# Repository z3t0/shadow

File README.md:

# SumoDuino 

### What is this repository for?
**Project Name: SumoDuino**

**Project Summary: AVR based project using to create a SumoBot**

**Version: 1.1**

### Features
* Seek and find navigation system
* Line-Sensing logic to keep robot in the ring
* Several InfraRed sensors to allow accurate seeking

### Credits
Rafi Khan, I am the owner and main contributor to this repository.
Email: zetoslab@gmail.com

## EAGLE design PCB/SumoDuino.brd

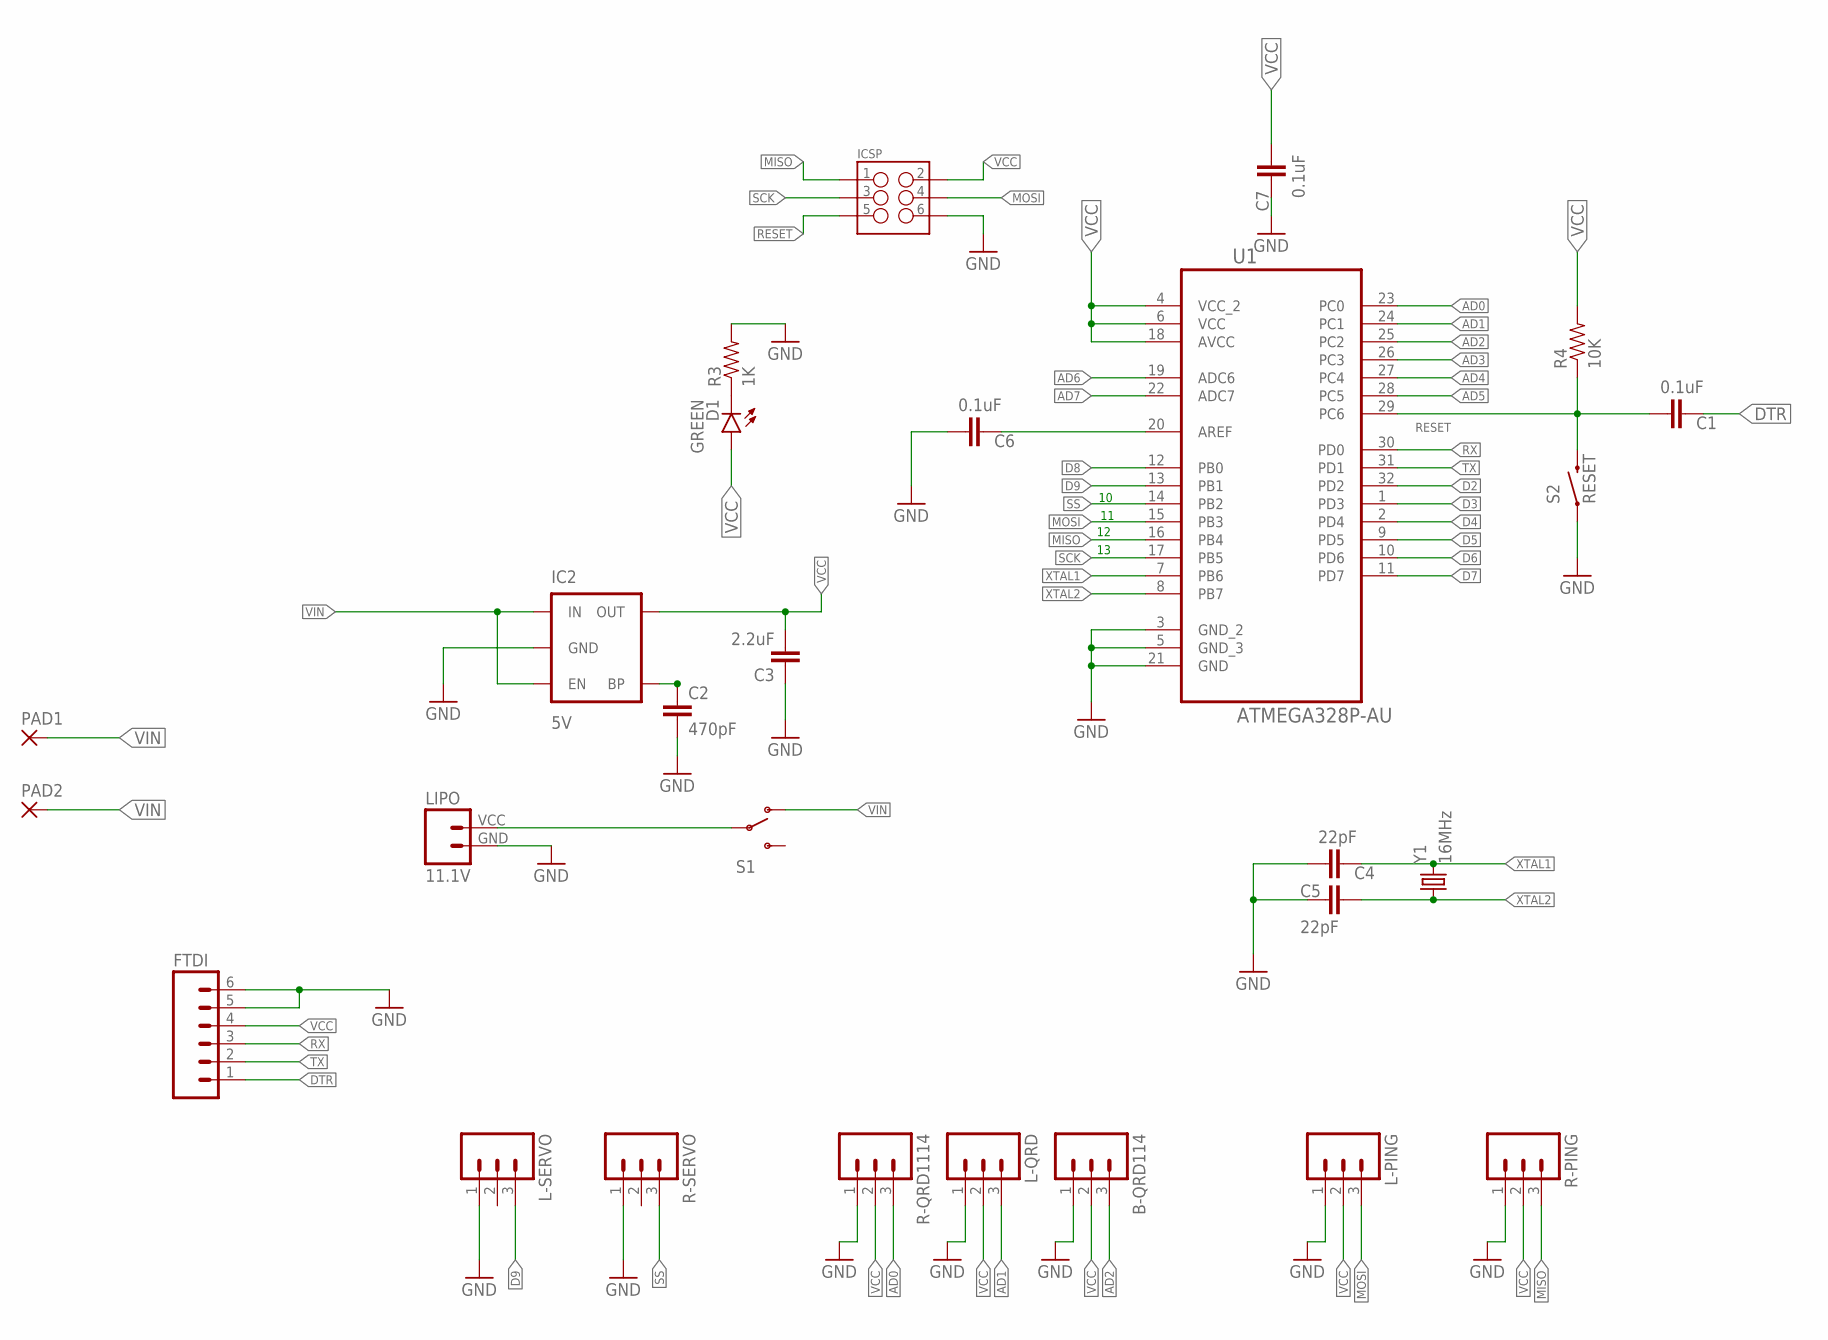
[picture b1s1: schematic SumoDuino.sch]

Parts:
B-QRD114: M03PTH; 1X03
C1, C6, C7: 0.1uF; 0603-CAP
C2: 470pF; 0603-CAP
C3: 2.2uF; 0603-CAP
C4, C5: 22pF; 0603-CAP
D1: GREEN; LED-0603
FTDI: M06LOCK; 1X06_LOCK
IC2: 5V; SOT23-5
ICSP: M03X22X3_SILK_MALE_PTH; 2X3
L-PING: M03PTH; 1X03
L-QRD: M03PTH; 1X03
L-SERVO: M03PTH; 1X03
LIPO: 11.1V; JST-2-SMD-VERT
PAD1, PAD2: 1,6/0,8
R3: 1K; 0603-RES
R4: 10K; 0603-RES
R-PING: M03PTH; 1X03
R-QRD1114: M03PTH; 1X03
R-SERVO: M03PTH; 1X03
S1: SWITCH-SPDTPTH; SWITCH-SPDT
S2: RESET; TACTILE-PTH
U1: ATMEGA328P-AU; QFP80P900X900X120-32N
Y1: 16MHz; HC49US

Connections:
AD0: R-QRD1114.3, U1.23 (PC0)
AD1: L-QRD.3, U1.24 (PC1)
AD2: B-QRD114.3, U1.25 (PC2)
AD3: U1.26 (PC3)
AD4: U1.27 (PC4)
AD5: U1.28 (PC5)
AD6: U1.19 (ADC6)
AD7: U1.22 (ADC7)
D2: U1.32 (PD2)
D3: U1.1 (PD3)
D4: U1.2 (PD4)
D5: U1.9 (PD5)
D6: U1.10 (PD6)
D7: U1.11 (PD7)
D8: U1.12 (PB0)
D9: L-SERVO.3, U1.13 (PB1)
DTR: C1.1, FTDI.1
GND: B-QRD114.1, C2.2, C3.1, C4.2, C5.2, C6.2, C7.1, FTDI.5, FTDI.6, IC2.2 (GND), ICSP.6, L-PING.1, L-QRD.1, L-SERVO.1, LIPO.GND (1), R3.2, R-PING.1, R-QRD1114.1, R-SERVO.1, S2.1, U1.3 (GND_2), U1.5 (GND_3), U1.21 (GND)
MISO: ICSP.1, R-PING.3, U1.16 (PB4)
MOSI: ICSP.4, L-PING.3, U1.15 (PB3)
unnamed: LIPO.VCC (2), S1.2
unnamed: D1.C, R3.1
unnamed: C2.1, IC2.4 (BP)
unnamed: C6.1, U1.20 (AREF)
RESET: C1.2, ICSP.5, R4.1, S2.3 (2), U1.29 (PC6)
RX: FTDI.3, U1.30 (PD0)
SCK: ICSP.3, U1.17 (PB5)
SS: R-SERVO.3, U1.14 (PB2)
TX: FTDI.2, U1.31 (PD1)
VCC: B-QRD114.2, C3.2, C7.2, D1.A, FTDI.4, IC2.5 (OUT), ICSP.2, L-PING.2, L-QRD.2, R4.2, R-PING.2, R-QRD1114.2, U1.4 (VCC_2), U1.6 (VCC), U1.18 (AVCC)
VIN: IC2.1 (IN), IC2.3 (EN), PAD1.1, PAD2.1, S1.1 (O)
XTAL1: C4.1, U1.7 (PB6), Y1.2
XTAL2: C5.1, U1.8 (PB7), Y1.1

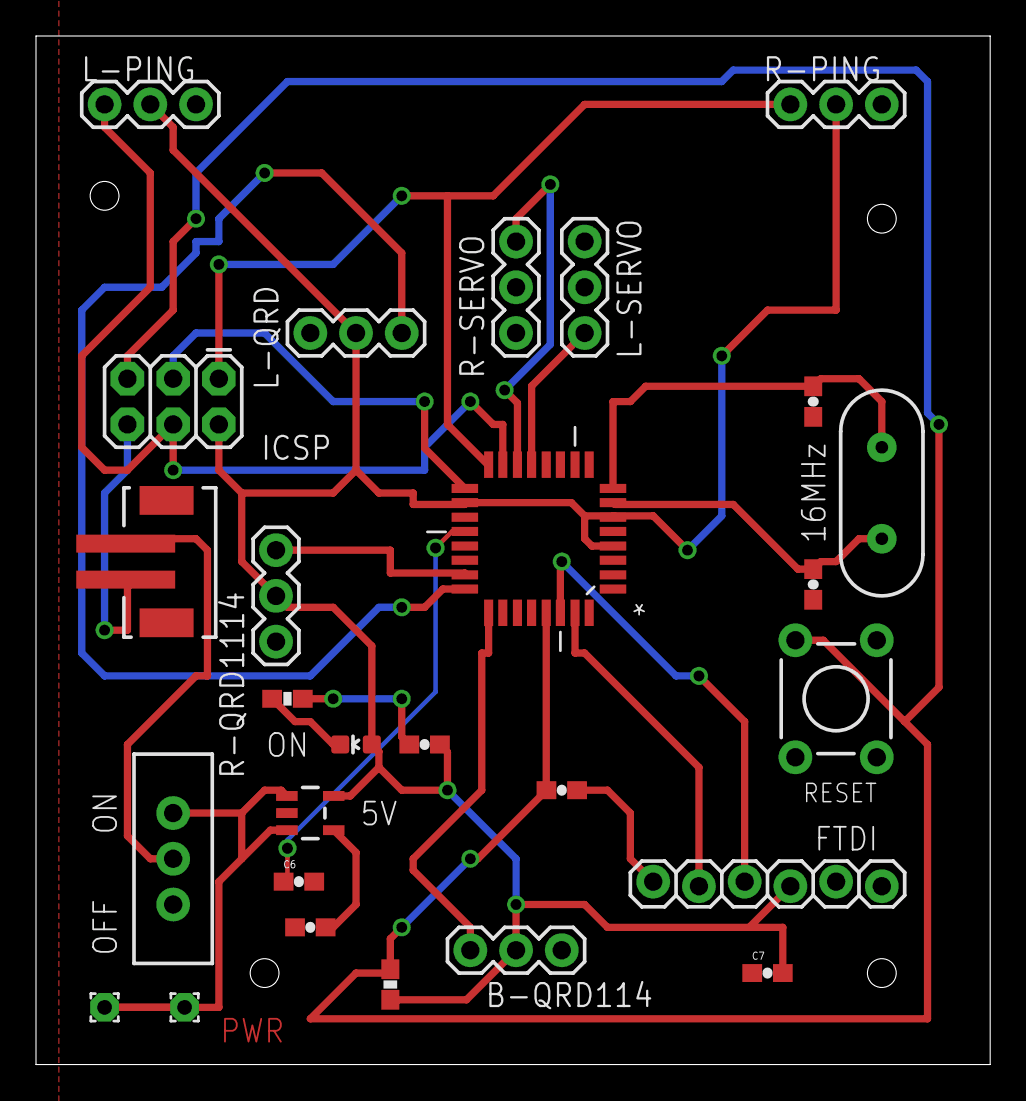
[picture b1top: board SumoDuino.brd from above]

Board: 2 copper layers, 53.0 x 57.1 mm, 27 parts (0 on the bottom side), 21 nets.

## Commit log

2015-02-19 Added beta scan/seek
2015-02-20 README.md edited online with Bitbucket
2015-02-20 Reorganized code and added PCB files
2015-02-20 Fixed navigation logic
2015-02-20 Message edit README.md
2015-02-21 remove wiki from repo
2015-02-21 Trying to figure out how to stop the wiki repository frombeing committed as a part of this repo.
2015-02-21 Still trying
2015-02-27 Added indentation
2015-03-05 SumoBot.ino edited online with Bitbucket
2015-03-06 Many changes, most importantly it is functional and also beta has been merged (OTR). Currently we still need to get navigation tuned but it is functional.
2017-02-06 cleaning up
2017-02-06 modified README
2017-02-06 setting up environment
2017-02-09 working on makefile
2017-02-19 can now upload to uno
2017-02-19 hide executable
2017-02-26 lots of cad
2017-02-26 more designs
2017-03-11 clean :
2017-03-11 restructuring
2017-03-11 adding kicad
2017-03-11 Failed library
2017-03-12 manual clone from template
2017-03-17 change port
2017-03-17 fixed debug led. it was only setting the ddrx, not the portx
2017-03-18 added rgb led, added two ir sensors
2017-03-19 working on timers
2017-03-19 reading distance from hc sr04. gave up on ping sensor
2017-03-19 working on stuff
2017-03-19 working sensor hc sr04 that is fully based on interrupts
2017-03-20 did a bunch of shit… working sonar, left right line detection. next need to work on motors
2017-03-22 added motor control, working on states. using spark fun board now. other one is fried on vin
2017-04-18 updated for blog

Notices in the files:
parts and their libraries:
SparkFun-PowerIC: Licensing: Creative Commons ShareAlike 4.0 International - https://creativecommons.org/licenses/by-sa/4.0
